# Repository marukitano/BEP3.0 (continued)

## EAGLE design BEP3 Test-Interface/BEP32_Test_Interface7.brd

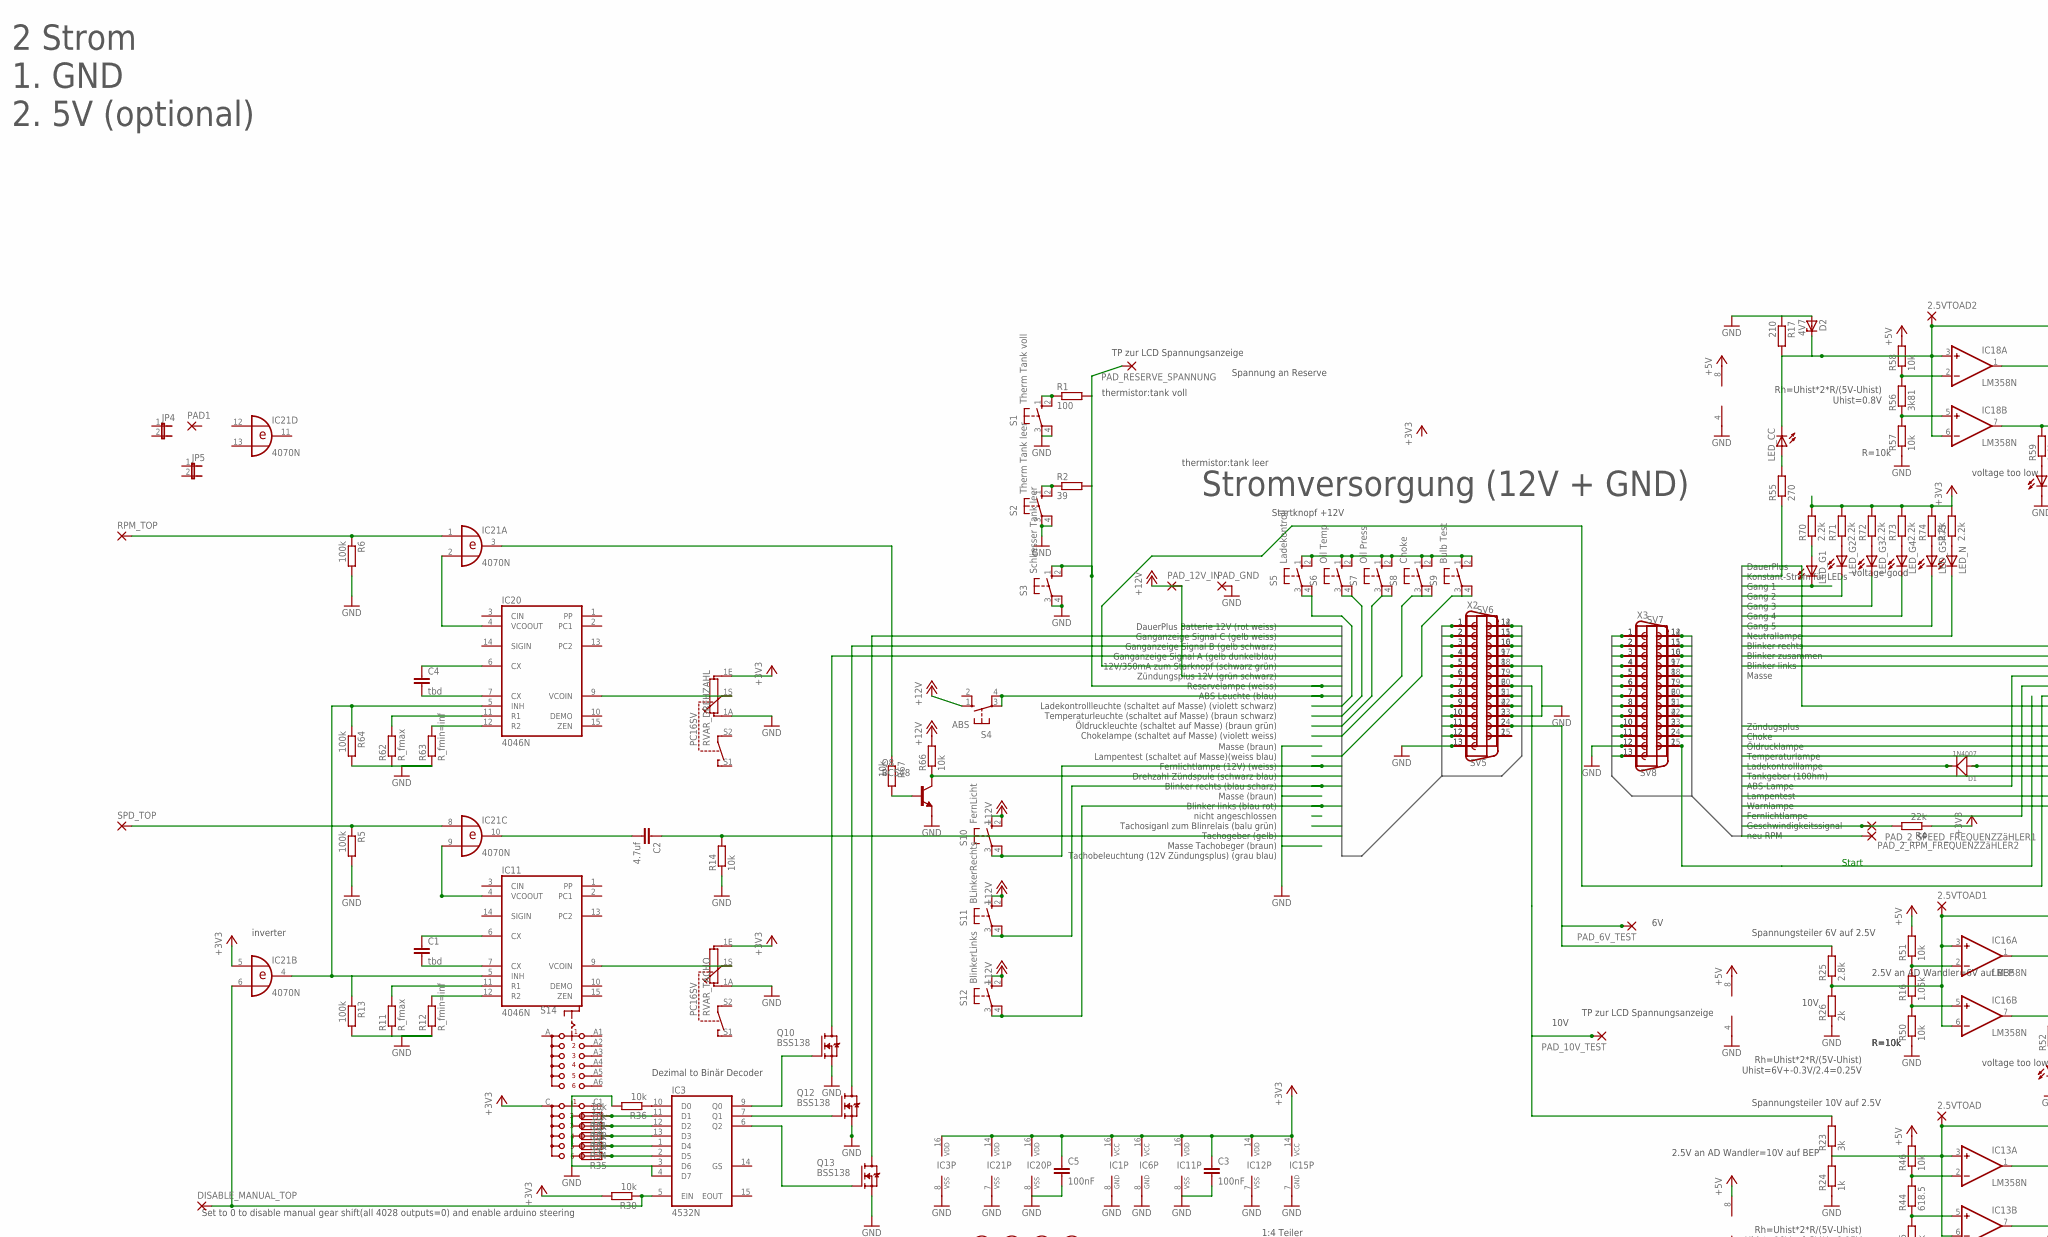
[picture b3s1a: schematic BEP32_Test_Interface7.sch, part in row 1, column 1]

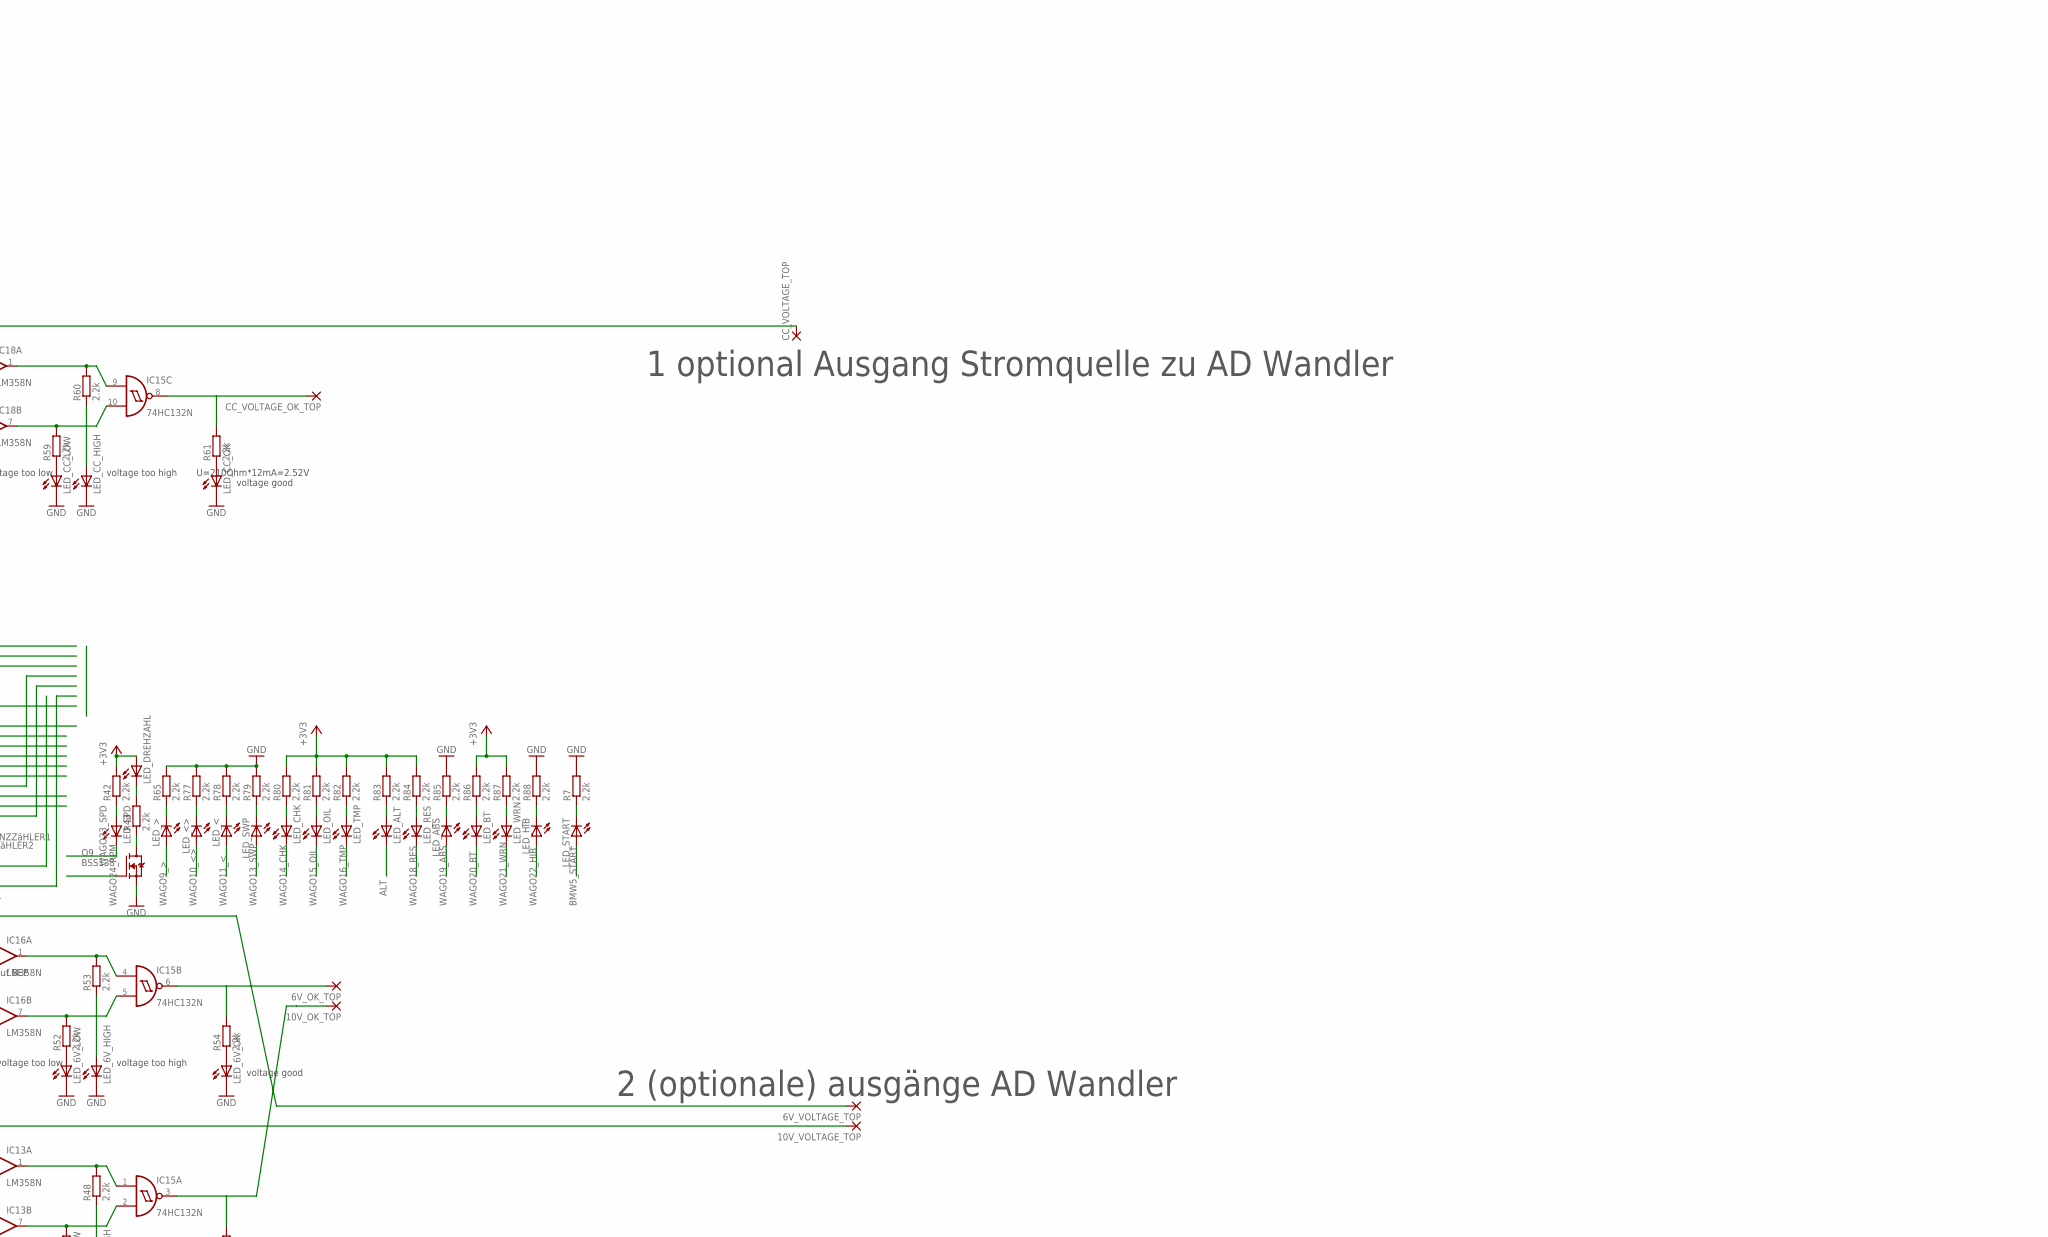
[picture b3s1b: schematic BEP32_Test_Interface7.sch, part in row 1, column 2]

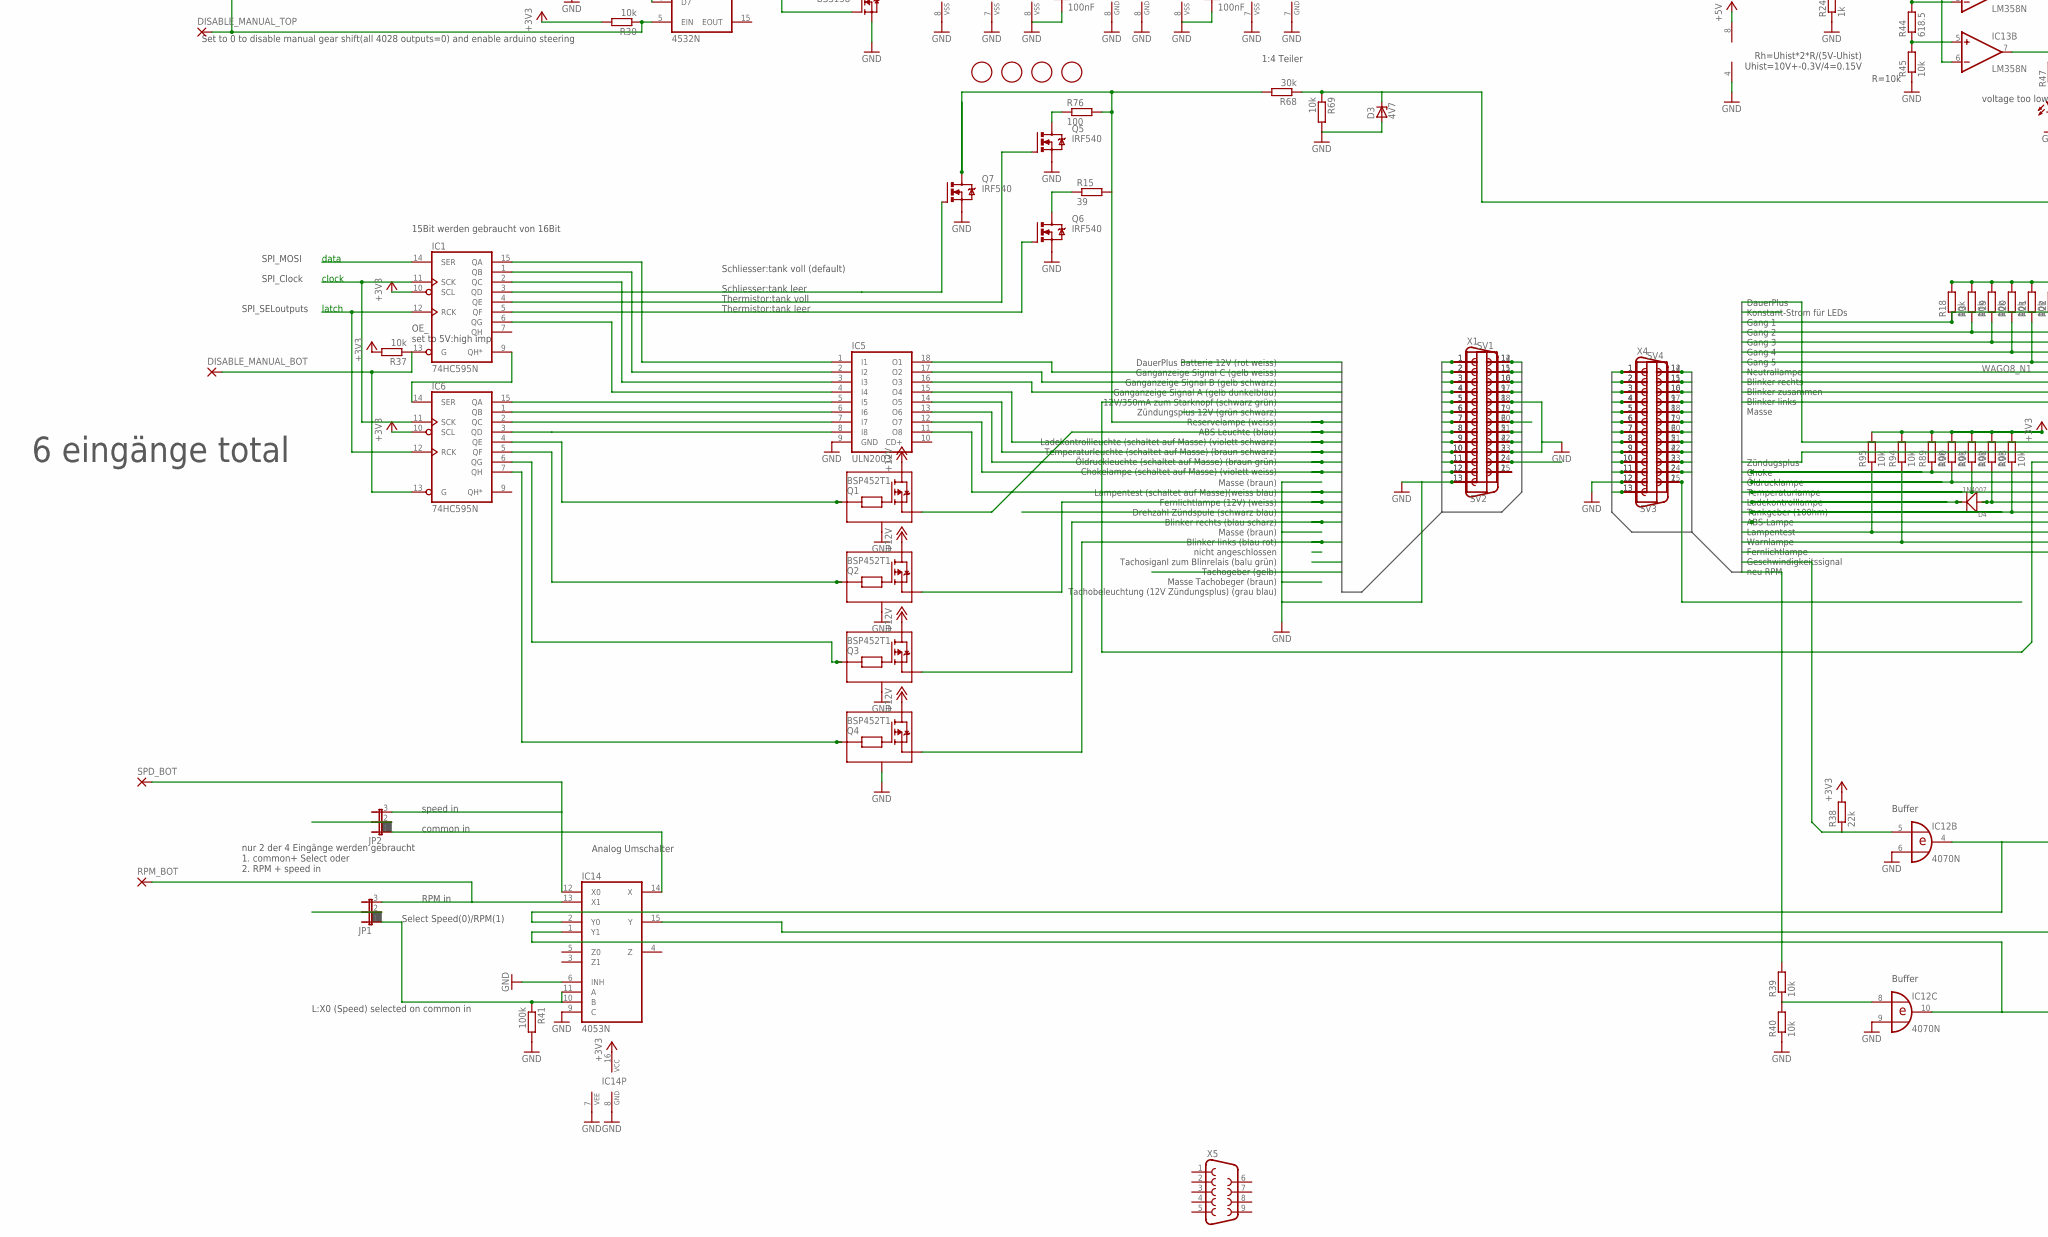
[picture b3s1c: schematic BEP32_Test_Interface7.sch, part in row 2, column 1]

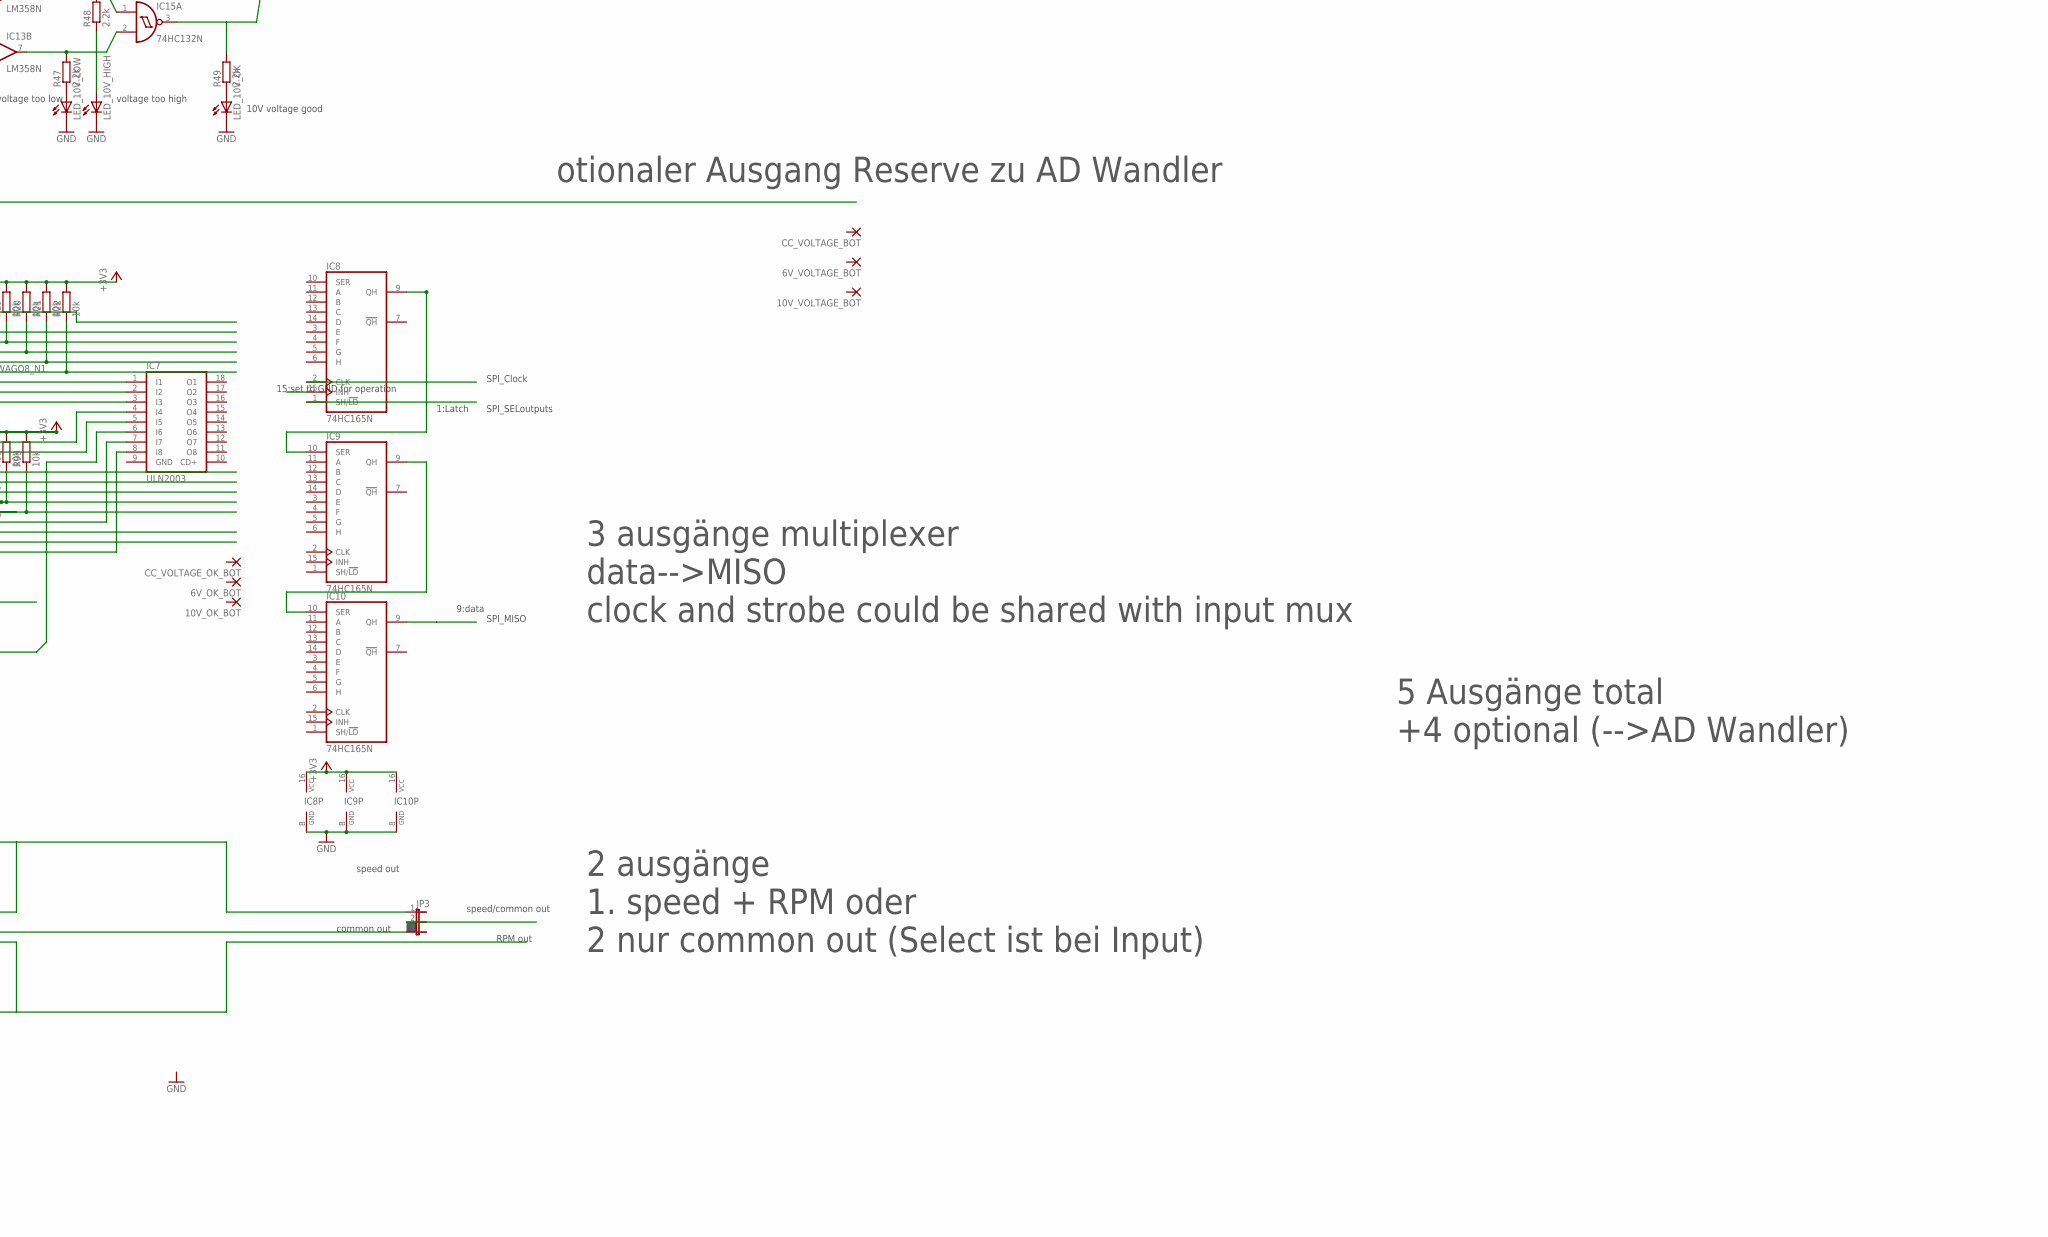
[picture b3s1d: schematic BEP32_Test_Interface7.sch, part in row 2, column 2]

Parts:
2.5VTOAD, 2.5VTOAD1, 2.5VTOAD2, 6V_OK_BOT, 6V_OK_TOP, 6V_VOLTAGE_BOT, 6V_VOLTAGE_TOP, 10V_OK_BOT, 10V_OK_TOP, 10V_VOLTAGE_BOT, 10V_VOLTAGE_TOP: 1,6/0,9
C1, C4: tbd; C1206K
C2: 4.7uf; C025_050-025X075
C3, C5: 100nF; C1206K
CC_VOLTAGE_BOT: 1,6/0,9
CC_VOLTAGE_OK_BOT: 1,6/0,9
CC_VOLTAGE_OK_TOP: 1,6/0,9
CC_VOLTAGE_TOP: 1,6/0,9
D1, D4: 1N4007; DO-214AC
D2, D3: 4V7; F126Z10
DISABLE_MANUAL_BOT: 1,6/0,9
DISABLE_MANUAL_TOP: 1,6/0,9
IC1, IC6: 74HC595N; DIL16
IC3: 4532N; DIL16
IC5, IC7: ULN2003; DIL18
IC8, IC9, IC10: 74HC165N; DIL16
IC11, IC20: 4046N; DIL16
IC12, IC21: 4070N; DIL14
IC13, IC16, IC18: LM358N; DIL08
IC14: 4053N; DIL16
IC15: 74HC132N; DIL14
JP1, JP2, JP3: JP2E; JP2
JP4, JP5: JP1E; JP1
LED_6V_HIGH, LED_6V_LOW, LED_6V_OK, LED_10V_HIGH, LED_10V_LOW, LED_10V_OK: LED5MM
LED_<: LED5MM
LED_<>: LED5MM
LED_>: LED5MM
LED_ABS: LED5MM
LED_ALT: LED5MM
LED_BT: LED5MM
LED_CC: LED5MM
LED_CC_HIGH: LED5MM
LED_CC_LOW: LED5MM
LED_CC_OK: LED5MM
LED_CHK: LED5MM
LED_DREHZAHL: LED5MM
LED_G1, LED_G2, LED_G3, LED_G4, LED_G5: LED5MM
LED_HIB: LED5MM
LED_N: LED5MM
LED_OIL: LED5MM
LED_RES: LED5MM
LED_SPD: LED5MM
LED_START: LED5MM
LED_SWP: LED5MM
LED_TMP: LED5MM
LED_WRN: LED5MM
PAD1: 1,6/0,9
PAD_2_RPM_FREQUENZZäHLER2, PAD_2_SPEED_FREQUENZZäHLER1, PAD_6V_TEST, PAD_10V_TEST, PAD_12V_IN: 1,6/0,9
PAD_GND: 1,6/0,9
PAD_RESERVE_SPANNUNG: 1,6/0,9
Q1, Q2, Q3, Q4: BSP452T1; SOT223
Q5, Q6, Q7: IRF540; TO220BV
Q8: BC548; TO92-EBC
Q9, Q10, Q12, Q13: BSS138; SOT23
R1, R76: 100; 0207/10
R2, R15: 39; 0207/10
R3, R14, R18, R19, R20, R21, R22, R30, R31, R32, R33, R34, R35, R36, R37, R39, R40, R45, R46, R50, R51, R57, R58, R66, R67, R69, R89, R90, R91, R92, R93, R94, R95: 10k; 0207/10
R4, R38: 22k; 0207/10
R5, R6, R13, R41, R64: 100k; 0207/10
R7, R42, R43, R47, R48, R49, R52, R53, R54, R59, R60, R61, R65, R70, R71, R72, R73, R74, R75, R77, R78, R79, R80, R81, R82, R83, R84, R85, R86, R87, R88: 2.2k; 0207/10
R11, R62: R_fmax; 0207/10
R12, R63: R_fmin=inf; 0207/10
R16: 1.05k; 0207/10
R17: 210; 0207/10
R23: 3k; 0207/10
R24: 1k; 0207/10
R25: 2.8k; 0207/10
R26: 2k; 0207/10
R44: 618.5; 0207/10
R55: 270; 0207/10
R56: 3k81; 0207/10
R68: 30k; 0207/10
RPM_BOT: 1,6/0,9
RPM_TOP: 1,6/0,9
RVAR_DREHZAHL: PC16SV
RVAR_TACHO: PC16SV
S1: Therm Tank voll; B3F-40XX
S2: Therm Tank leer; B3F-40XX
S3: Schliesser Tank leer; B3F-40XX
S4: ABS; B3F-40XX
S5: Ladekontroll; B3F-40XX
S6: Oil Temp; B3F-40XX
S7: Oil Press; B3F-40XX
S8: Choke; B3F-40XX
S9: Bulb Test; B3F-40XX
S10: FernLicht; B3F-40XX
S11: BLinkerRechts; B3F-40XX
S12: BlinkerLinks; B3F-40XX
S14: CK102X06
SPD_BOT: 1,6/0,9
SPD_TOP: 1,6/0,9
SV1, SV4, SV6, SV7: MA12-1
SV2, SV3, SV5, SV8: MA13-1
U$1, U$2, U$3, U$4: FIDUCIAL; FIDUCIAL_1MM
X1, X2, X3, X4: F25H
X5: F09H

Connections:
+3V3: C3.1, C5.1, IC1.10 (SCL), IC1.16 (VCC), IC3.16 (VDD), IC6.10 (SCL), IC6.16 (VCC), IC8.16 (VCC), IC9.16 (VCC), IC10.16 (VCC), IC11.16 (VDD), IC12.14 (VDD), IC14.16 (VCC), IC15.14 (VCC), IC20.16 (VDD), IC21.5 (I0), IC21.14 (VDD), LED_DREHZAHL.A, R3.2, R4.1, R18.2, R19.2, R20.2, R21.2, R22.2, R30.2, R37.2, R38.2, R42.2, R70.2, R71.2, R72.2, R73.2, R74.2, R75.2, R80.2, R81.2, R82.2, R83.2, R84.2, R86.2, R87.2, R89.2, R90.2, R91.2, R92.2, R93.2, R94.2, R95.2, RVAR_DREHZAHL.1E, RVAR_TACHO.1E, S14.C
+5V: IC13.8 (V+), IC16.8 (V+), IC18.8 (V+), R46.2, R51.2, R58.2
+12V: Q1.4 (V+), Q2.4 (V+), Q3.4 (V+), Q4.4 (V+), R66.2, S4.1 (S), S10.1 (S), S10.2 (S1), S11.1 (S), S11.2 (S1), S12.1 (S), S12.2 (S1)
ALT: D1.1 (+), LED_ALT.K (C)
ALT1: D4.1 (+), R92.1
BMW1_12V: PAD_12V_IN.1, SV5.1, X2.1
BMW1_12V1: SV2.1, X1.1
BMW2_C: Q13.3 (D), SV5.2, X2.2
BMW2_C1: IC5.18 (O1), SV2.2, X1.2
BMW3_B: Q12.3 (D), SV5.3, X2.3
BMW3_B1: IC5.17 (O2), SV2.3, X1.3
BMW4_A: Q10.3 (D), SV5.4, X2.4
BMW4_A1: IC5.16 (O3), SV2.4, X1.4
BMW5_START: LED_START.A, SV5.5, X2.5
BMW5_START1: IC7.6 (I6), SV2.5, X1.5
BMW6_ZP: SV5.6, X2.6
BMW6_ZP1: SV2.6, X1.6
BMW7_RES: PAD_RESERVE_SPANNUNG.1, R1.2, R2.2, S3.1 (S), S3.2 (S1), SV5.7, X2.7
BMW7_RES1: Q7.D, R68.2, R76.2, SV2.7, X1.7
BMW8_ABS: S4.3, S4.4 (P1), SV5.8, X2.8
BMW8_ABS1: Q1.1 (OUT), SV2.8, X1.8
BMW9_ALT: S5.3, S5.4 (P1), SV5.9, X2.9
BMW9_ALT1: IC5.15 (O4), SV2.9, X1.9
BMW10_TMP: S6.3, S6.4 (P1), SV5.10, X2.10
BMW10_TMP1: IC5.14 (O5), SV2.10, X1.10
BMW11_OIL: S7.3, S7.4 (P1), SV5.11, X2.11
BMW11_OIL1: IC5.13 (O6), SV2.11, X1.11
BMW12_CHK: S8.3, S8.4 (P1), SV5.12, X2.12
BMW12_CHK1: IC5.12 (O7), SV2.12, X1.12
BMW14_BT: S9.3, S9.4 (P1), SV6.12, X2.14
BMW14_BT1: IC5.11 (O8), SV1.12, X1.14
BMW15_HIB: S10.3, S10.4 (P1), SV6.11, X2.15
BMW15_HIB1: Q2.1 (OUT), SV1.11, X1.15
BMW16_RPM: Q8.C, R66.1, SV6.10, X2.16
BMW16_RPM1: SV1.10, X1.16
BMW17_>: S11.3, S11.4 (P1), SV6.9, X2.17
BMW17_>1: Q3.1 (OUT), SV1.9, X1.17
BMW19_<: S12.3, S12.4 (P1), SV6.7, X2.19
BMW19_<1: Q4.1 (OUT), SV1.7, X1.19
BMW21_SPDBACK: SV6.5, X2.21
BMW21_SPDBACK1: SV1.5, X1.21
BMW22_SPD: C2.1, R14.2, SV6.4, X2.22
BMW22_SPD1: SV1.4, X1.22
BMW24_10V: PAD_10V_TEST.1, R23.2, SV6.6, X2.20
BMW24_10V1: SV1.6, X1.20
DISABLE_MANUAL: DISABLE_MANUAL_TOP.1, IC3.5 (EIN), IC21.6 (I1), R30.1
DISABLE_MANUAL_BOT: DISABLE_MANUAL_BOT.1, IC1.13 (G), IC6.13 (G), R37.1
GND: C3.2, C5.2, D2.A, D3.A, IC1.8 (GND), IC3.3 (D6), IC3.4 (D7), IC3.8 (VSS), IC5.9 (GND), IC6.8 (GND), IC7.9 (GND), IC8.8 (GND), IC9.8 (GND), IC10.8 (GND), IC11.8 (VSS), IC12.6 (I1), IC12.7 (VSS), IC12.9 (I1), IC13.4 (V-), IC14.6 (INH), IC14.7 (VEE), IC14.8 (GND), IC14.9 (C), IC15.7 (GND), IC16.4 (V-), IC18.4 (V-), IC20.8 (VSS), IC21.7 (VSS), LED_6V_HIGH.K (C), LED_6V_LOW.K (C), LED_6V_OK.K (C), LED_10V_HIGH.K (C), LED_10V_LOW.K (C), LED_10V_OK.K (C), LED_CC_HIGH.K (C), LED_CC_LOW.K (C), LED_CC_OK.K (C), PAD_GND.1, Q1.2 (GND), Q2.2 (GND), Q3.2 (GND), Q4.2 (GND), Q5.S, Q6.S, Q7.S, Q8.E, Q9.2 (S), Q10.2 (S), Q12.2 (S), Q13.2 (S), R5.2, R6.2, R7.2, R11.1, R12.1, R13.2, R14.1, R17.1, R24.1, R26.1, R31.2, R32.2, R33.2, R34.2, R35.2, R36.2, R40.1, R41.2, R45.1, R50.1, R57.1, R62.1, R63.1, R64.2, R65.2, R69.2, R77.2, R78.2, R79.2, R85.2, R88.2, RVAR_DREHZAHL.1A, RVAR_TACHO.1A, S1.3, S1.4 (P1), S2.3, S2.4 (P1), S3.3, S3.4 (P1), SV1.3, SV1.8, SV2.13, SV3.12, SV5.13, SV6.3, SV6.8, SV8.12, X1.13, X1.18, X1.23, X2.13, X2.18, X2.23, X3.12, X4.12
unnamed: R2.1, S2.1 (S), S2.2 (S1)
unnamed: R1.1, S1.1 (S), S1.2 (S1)
unnamed: LED_>.K (C), R65.1
unnamed: LED_<>.K (C), R77.1
unnamed: LED_<.K (C), R78.1
unnamed: IC1.15 (QA), IC5.1 (I1)
unnamed: IC1.1 (QB), IC5.2 (I2)
unnamed: IC1.2 (QC), IC5.3 (I3)
unnamed: IC11.5 (INH), IC20.5 (INH), IC21.4 (O), R13.1, R64.1
unnamed: IC14.12 (X0), JP2.3, SPD_BOT.1
unnamed: IC21.1 (I0), R6.1, RPM_TOP.1
unnamed: IC3.9 (Q0), Q10.1 (G)
unnamed: IC3.6 (Q2), Q13.1 (G)
unnamed: IC1.3 (QD), Q7.G
unnamed: IC1.4 (QE), Q5.G
unnamed: IC1.9 (QH*), IC6.14 (SER)
unnamed: IC1.12 (RCK), IC6.12 (RCK)
unnamed: S5.1 (S), S5.2 (S1), S6.1 (S), S6.2 (S1), S7.1 (S), S7.2 (S1), S8.1 (S), S8.2 (S1), S9.1 (S), S9.2 (S1)
unnamed: IC8.9 (QH), IC9.10 (SER)
unnamed: Q6.D, R15.1
unnamed: IC1.6 (QG), IC5.4 (I4)
unnamed: IC5.5 (I5), IC6.15 (QA)
unnamed: IC5.6 (I6), IC6.1 (QB)
unnamed: IC5.7 (I7), IC6.2 (QC)
unnamed: IC5.8 (I8), IC6.3 (QD)
unnamed: IC6.4 (QE), Q1.3 (IN)
unnamed: IC6.5 (QF), Q2.3 (IN)
unnamed: IC6.6 (QG), Q3.3 (IN)
unnamed: IC6.7 (QH), Q4.3 (IN)
unnamed: C1.2, IC11.7 (CX)
unnamed: C1.1, IC11.6 (CX)
unnamed: IC11.11 (R1), R11.2
unnamed: IC11.12 (R2), R12.2
unnamed: C2.2, IC21.10 (O)
unnamed: IC1.5 (QF), Q6.G
unnamed: LED_G1.A, R70.1
unnamed: IC11.9 (VCOIN), RVAR_TACHO.1S
unnamed: IC21.8 (I0), R5.1, SPD_TOP.1
unnamed: LED_WRN.A, R87.1
unnamed: 2.5VTOAD2.1, CC_VOLTAGE_TOP.1, D2.C, IC18.3 (+IN), IC18.6 (-IN), LED_CC.K (C), R17.2
unnamed: IC16.5 (+IN), R16.1, R50.2
unnamed: 2.5VTOAD1.1, 6V_VOLTAGE_TOP.1, IC16.3 (+IN), IC16.6 (-IN), R25.1, R26.2
unnamed: IC14.14 (X), JP2.1
unnamed: IC9.9 (QH), IC10.10 (SER)
unnamed: IC3.11 (D1), R31.1, S14.C2
unnamed: IC3.12 (D2), R32.1, S14.C3
unnamed: IC3.13 (D3), R33.1, S14.C4
unnamed: IC3.1 (D4), R34.1, S14.C5
unnamed: IC3.2 (D5), R35.1, S14.C6
unnamed: IC3.10 (D0), R36.1
unnamed: IC14.10 (B), IC14.11 (A), JP1.1, R41.1
unnamed: IC14.15 (Y), JP3.3
unnamed: Q9.3 (D), R43.1
unnamed: IC14.13 (X1), JP1.3, RPM_BOT.1
unnamed: IC12.8 (I0), R39.1, R40.2
unnamed: LED_ABS.K (C), R85.1
unnamed: LED_HIB.K (C), R88.1
unnamed: LED_DREHZAHL.K (C), R43.2
unnamed: IC13.5 (+IN), R44.1, R45.2
unnamed: IC13.2 (-IN), R44.2, R46.1
unnamed: 2.5VTOAD.1, 10V_VOLTAGE_TOP.1, IC13.3 (+IN), IC13.6 (-IN), R23.1, R24.2
unnamed: IC16.2 (-IN), R16.2, R51.1
unnamed: IC13.1 (OUT), IC15.1 (I0), R48.2
unnamed: IC13.7 (OUT), IC15.2 (I1), R47.2
unnamed: LED_10V_LOW.A, R47.1
unnamed: LED_10V_HIGH.A, R48.1
unnamed: LED_10V_OK.A, R49.1
unnamed: 10V_OK_TOP.1, IC15.3 (O), R49.2
unnamed: IC11.4 (VCOOUT), IC21.9 (I1)
unnamed: IC15.4 (I0), IC16.1 (OUT), R53.2
unnamed: IC15.5 (I1), IC16.7 (OUT), R52.2
unnamed: LED_6V_LOW.A, R52.1
unnamed: LED_6V_HIGH.A, R53.1
unnamed: LED_6V_OK.A, R54.1
unnamed: 6V_OK_TOP.1, IC15.6 (O), R54.2
unnamed: LED_CC.A, R55.2
unnamed: IC18.5 (+IN), R56.1, R57.2
unnamed: IC18.2 (-IN), R56.2, R58.1
unnamed: C4.2, IC20.7 (CX)
unnamed: IC15.9 (I0), IC18.1 (OUT), R60.2
unnamed: IC15.10 (I1), IC18.7 (OUT), R59.2
unnamed: LED_CC_LOW.A, R59.1
unnamed: LED_CC_HIGH.A, R60.1
unnamed: LED_CC_OK.A, R61.1
unnamed: CC_VOLTAGE_OK_TOP.1, IC15.8 (O), R61.2
unnamed: C4.1, IC20.6 (CX)
unnamed: IC20.11 (R1), R62.2
unnamed: IC20.12 (R2), R63.2
unnamed: IC20.4 (VCOOUT), IC21.2 (I1)
unnamed: LED_SWP.K (C), R79.1
unnamed: PAD_6V_TEST.1, R25.2, SV6.2, X2.24
unnamed: SV1.2, X1.24
unnamed: LED_START.K (C), R7.1
unnamed: IC20.9 (VCOIN), RVAR_DREHZAHL.1S
unnamed: Q5.D, R76.1
unnamed: IC21.3 (O), R67.1
unnamed: Q8.B, R67.2
unnamed: LED_G2.A, R71.1
unnamed: D3.C, R68.1, R69.1
unnamed: LED_G3.A, R72.1
unnamed: LED_G4.A, R73.1
unnamed: LED_G5.A, R74.1
unnamed: LED_N.A, R75.1
unnamed: LED_CHK.A, R80.1
unnamed: LED_OIL.A, R81.1
unnamed: LED_TMP.A, R82.1
unnamed: LED_ALT.A, R83.1
unnamed: LED_RES.A, R84.1
unnamed: LED_SPD.A, R42.1
unnamed: LED_BT.A, R86.1
unnamed: SV1.1, X1.25
unnamed: SV6.1, X2.25
unnamed: IC3.7 (Q1), Q12.1 (G)
RPM_4070N: IC12.10 (O), IC14.1 (Y1)
SPD_4070N: IC12.4 (O), IC14.2 (Y0), JP3.1
SPI_CLK: IC1.11 (SCK), IC6.11 (SCK)
WAGO1_BAT: SV8.1, X3.1
WAGO1_BAT1: IC7.4 (I4), SV3.1, X4.1
WAGO2_CC: R55.1, SV8.2, X3.2
WAGO2_CC1: SV3.2, X4.2
WAGO3_G1: LED_G1.K (C), SV8.3, X3.3
WAGO3_G1.: R18.1, SV3.3, X4.3
WAGO4_G2: LED_G2.K (C), SV8.4, X3.4
WAGO4_G2.: R3.1, SV3.4, X4.4
WAGO5_G3: LED_G3.K (C), SV8.5, X3.5
WAGO5_G3.: R19.1, SV3.5, X4.5
WAGO6_G4: LED_G4.K (C), SV8.6, X3.6
WAGO6_G4.: R20.1, SV3.6, X4.6
WAGO7_G5: LED_G5.K (C), SV8.7, X3.7
WAGO7_G5.: R21.1, SV3.7, X4.7
WAGO8_N: LED_N.K (C), SV8.8, X3.8
WAGO8_N1: R22.1, SV3.8, X4.8
WAGO9_>: LED_>.A, SV8.9, X3.9
WAGO9_>1: IC7.1 (I1), SV3.9, X4.9
WAGO10_<>: LED_<>.A, SV8.10, X3.10
WAGO10_<>1: IC7.2 (I2), SV3.10, X4.10
WAGO11_<: LED_<.A, SV8.11, X3.11
WAGO11_<1: IC7.3 (I3), SV3.11, X4.11
WAGO13_SWP: LED_SWP.A, SV8.13, X3.13
WAGO13_SWP1: IC7.5 (I5), SV3.13, X4.13
WAGO14_CHK: LED_CHK.K (C), SV7.12, X3.14
WAGO14_CHK1: R89.1, SV4.12, X4.14
WAGO15_OIL: LED_OIL.K (C), SV7.11, X3.15
WAGO15_OIL1: R90.1, SV4.11, X4.15
WAGO16_TMP: LED_TMP.K (C), SV7.10, X3.16
WAGO16_TMP1: R91.1, SV4.10, X4.16
WAGO17_ALT: D1.2 (-), SV7.9, X3.17
WAGO17_ALT1: D4.2 (-), SV4.9, X4.17
WAGO18_RES: LED_RES.K (C), SV7.8, X3.18
WAGO18_RES1: R93.1, SV4.8, X4.18
WAGO19_ABS: LED_ABS.A, SV7.7, X3.19
WAGO19_ABS1: IC7.7 (I7), SV4.7, X4.19
WAGO20_BT: LED_BT.K (C), SV7.6, X3.20
WAGO20_BT1: R95.1, SV4.6, X4.20
WAGO21_WRN: LED_WRN.K (C), SV7.5, X3.21
WAGO21_WRN1: R94.1, SV4.5, X4.21
WAGO22_HIB: LED_HIB.A, SV7.4, X3.22
WAGO22_HIB1: IC7.8 (I8), SV4.4, X4.22
WAGO23_SPD: LED_SPD.K (C), PAD_2_SPEED_FREQUENZZäHLER1.1, R4.2, SV7.3, X3.23
WAGO23_SPD1: IC12.5 (I0), R38.1, SV4.3, X4.23
WAGO24_RPM: PAD_2_RPM_FREQUENZZäHLER2.1, Q9.1 (G), SV7.2, X3.24
WAGO24_RPM1: R39.2, SV4.2, X4.24
WAGO25_START: SV7.1, X3.25
WAGO25_START1: SV4.1, X4.25

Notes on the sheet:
Zündugsplus Choke Öldrucklampe Temperaturlampe Ladekontrolllampe Tankgeber (100hm) ABS-Lampe Lampentest Warnlampe Fernlichtlampe Geschwindigkeitssignal neu RPM
DauerPlus Konstant-Strom für LEDs Gang 1 Gang 2 Gang 3 Gang 4 Gang 5 Neutrallampe Blinker rechts Blinker zusammen Blinker links Masse
DauerPlus Batterie 12V (rot weiss) Ganganzeige Signal C (gelb weiss) Ganganzeige Signal B (gelb schwarz) Ganganzeige Signal A (gelb dunkelblau) 12V/350mA zum Starknopf (schwarz grün) Zündungsplus 12V (grün schwarz) Reservelampe (weiss) ABS Leuchte (blau) Ladekontrollleuchte (schaltet auf Masse) (vi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
Masse (braun) Lampentest (schaltet auf Masse)(weiss blau) Fernlichtlampe (12V) (weiss) Drehzahl Zündspule (schwarz blau) Blinker rechts (blau scharz) Masse (braun) Blinker links (blau rot) nicht angeschlossen Tachosiganl zum Blinrelais (balu grün) Tachogeber (gelb) Masse Tachobeger (braun) Tachobel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
Start
10V
Dezimal to Binär Decoder
data
clock
OE_ set to 5V:high imp
latch
thermistor:tank leer
thermistor:tank voll
Schliesser:tank leer
Schliesser:tank voll (default)
Startknopf +12V
15Bit werden gebraucht von 16Bit
Spannung an Reserve
2.5V an AD Wandler=6V auf BEP
Spannungsteiler 6V auf 2.5V
Set to 0 to disable manual gear shift(all 4028 outputs=0) and enable arduino steering
SPI_MOSI
SPI_Clock
SPI_SELoutputs
L:X0 (Speed) selected on common in
common in
speed in
RPM in
common out
speed out
Buffer
RPM out
Analog Umschalter
nur 2 der 4 Eingänge werden gebraucht 1. common+ Select oder 2. RPM + speed in
6 eingänge total
3 ausgänge multiplexer data-->MISO clock and strobe could be shared with input mux
2 (optionale) ausgänge AD Wandler
2 ausgänge 1. speed + RPM oder 2 nur common out (Select ist bei Input)
2 Strom 1. GND 2. 5V (optional)
Stromversorgung (12V + GND)

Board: 2 copper layers, 225 parts (0 on the bottom side), 212 nets, no tracks yet.

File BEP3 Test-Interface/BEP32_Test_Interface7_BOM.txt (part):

Stückliste exportiert aus D:/marulabs/Layout_Eagle/BEP3 Test-Interface/BEP32_Test_Interface7.sch am 18.02.2018 18:58

Part                        Value                Device                             Package          Description                                                             MF                   MPN      OC_FARNELL OC_NEWARK VALUE 
2.5VTOAD                                         1,6/0,9                            1,6/0,9          THROUGH-HOLE PAD                                                                                                                 
2.5VTOAD1                                        1,6/0,9                            1,6/0,9          THROUGH-HOLE PAD                                                                                                                 
2.5VTOAD2                                        1,6/0,9                            1,6/0,9          THROUGH-HOLE PAD                                                                                                                 
6V_OK_BOT                                        1,6/0,9                            1,6/0,9          THROUGH-HOLE PAD                                                                                                                 
6V_OK_TOP                                        1,6/0,9                            1,6/0,9          THROUGH-HOLE PAD                                                                                                                 
6V_VOLTAGE_BOT                                   1,6/0,9                            1,6/0,9          THROUGH-HOLE PAD                                                                                                                 
6V_VOLTAGE_TOP                                   1,6/0,9                            1,6/0,9          THROUGH-HOLE PAD                                                                                                                 
10V_OK_BOT                                       1,6/0,9                            1,6/0,9          THROUGH-HOLE PAD                                                                                                                 
10V_OK_TOP                                       1,6/0,9                            1,6/0,9          THROUGH-HOLE PAD                                                                                                                 
10V_VOLTAGE_BOT                                  1,6/0,9                            1,6/0,9          THROUGH-HOLE PAD                                                                                                                 
10V_VOLTAGE_TOP                                  1,6/0,9                            1,6/0,9          THROUGH-HOLE PAD                                                                                                                 
C1                          tbd                  C-EUC1206K                         C1206K           CAPACITOR, European symbol                                                                                                       
C2                          4.7uf                C-EU025_050-025X075                C025_050-025X075 CAPACITOR, European symbol                                                                                                       
C3                          100nF                C-EUC1206K                         C1206K           CAPACITOR, European symbol                                                                                                       
C4                          tbd                  C-EUC1206K                         C1206K           CAPACITOR, European symbol                                                                                                       
C5                          100nF                C-EUC1206K                         C1206K           CAPACITOR, European symbol                                                                                                       
CC_VOLTAGE_BOT                                   1,6/0,9                            1,6/0,9          THROUGH-HOLE PAD                                                                                                                 
CC_VOLTAGE_OK_BOT                                1,6/0,9                            1,6/0,9          THROUGH-HOLE PAD                                                                                                                 
CC_VOLTAGE_OK_TOP                                1,6/0,9                            1,6/0,9          THROUGH-HOLE PAD                                                                                                                 
CC_VOLTAGE_TOP                                   1,6/0,9                            1,6/0,9          THROUGH-HOLE PAD                                                                                                                 
D1                          1N4007               DIODE-GEN-PURPOSE-1KV-1A(DO-214AC) DO-214AC         304010013                                                                                    1N4007                        1N4007
D2                          4V7                  ZENER-DIODEF126-10                 F126Z10          Z-Diode                                                                                                                          
D3                          4V7                  ZENER-DIODEF126-10                 F126Z10          Z-Diode                                                                                                                          
D4                          1N4007               DIODE-GEN-PURPOSE-1KV-1A(DO-214AC) DO-214AC         304010013                                                                                    1N4007                        1N4007
DISABLE_MANUAL_BOT                               1,6/0,9                            1,6/0,9          THROUGH-HOLE PAD                                                                                                                 
DISABLE_MANUAL_TOP                               1,6/0,9                            1,6/0,9          THROUGH-HOLE PAD                                                                                                                 
IC1                         74HC595N             74HC595N                           DIL16            8-bit SHIFT REGISTER, output latch                                                                                               
IC3                         4532N                4532N                              DIL16            8-bit PRIORITY ENCODER                                                                                                           
IC5                         ULN2003              ULN2803A                           DIL18            DRIVER ARRAY                                                                                                                     
IC6                         74HC595N             74HC595N                           DIL16            8-bit SHIFT REGISTER, output latch                                                                                               
IC7                         ULN2003              ULN2803A                           DIL18            DRIVER ARRAY                                                                                                                     
IC8                         74HC165N             74HC165N                           DIL16            8-bit parallel load SHIFT REGISTER                                                                                               
IC9                         74HC165N             74HC165N                           DIL16            8-bit parallel load SHIFT REGISTER                                                                                               
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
